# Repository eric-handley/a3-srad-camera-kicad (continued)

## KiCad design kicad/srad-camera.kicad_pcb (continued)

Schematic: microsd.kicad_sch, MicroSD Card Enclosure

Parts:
C151: 100nF; C_0402_1005Metric; LCSC PART NAME C1525
C152: 1uF; C_0603_1608Metric; LCSC PART NAME C15849
C153: 10uF; C_0805_2012Metric; LCSC PART NAME C15850
D3, D4, D5, D6, D7, D8, D9: TVS Vr3.3 Vb4; D_SOD-123F; LCSC PART NAME C19077496
R53, R54, R55, R56, R57, R58: 22R; R_0402_1005Metric; LCSC PART NAME C25092
SD1: MOLEX 472192001; microSD_HC_Molex_47219-2001

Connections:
/MicroSD Port/CLK: R56.1; also elsewhere on the board
/MicroSD Port/CMD: R55.1; also elsewhere on the board
/MicroSD Port/D0: R57.1; also elsewhere on the board
/MicroSD Port/D1: R58.1; also elsewhere on the board
/MicroSD Port/D2: R53.1; also elsewhere on the board
/MicroSD Port/D3: R54.1; also elsewhere on the board
GND: C151.2, C152.2, C153.1, D3.1 (A1), D4.1 (A1), D5.1 (A1), D6.1 (A1), D7.1 (A1), D8.1 (A1), D9.1 (A1), SD1.6 (VSS), SD1.10 (SHIELD); also elsewhere on the board
unnamed: D3.2 (A2), R58.2, SD1.8 (DAT1)
unnamed: D4.2 (A2), R57.2, SD1.7 (DAT0)
unnamed: D5.2 (A2), R56.2, SD1.5 (CLK)
unnamed: D6.2 (A2), R55.2, SD1.3 (CMD)
unnamed: D7.2 (A2), R54.2, SD1.2 (DAT3/CD)
unnamed: D8.2 (A2), R53.2, SD1.1 (DAT2)
VCC_3V3_SD: C151.1, C152.1, C153.2, D9.2 (A2), SD1.4 (VDD); also elsewhere on the board

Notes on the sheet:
DET not needed as MicroSD always present

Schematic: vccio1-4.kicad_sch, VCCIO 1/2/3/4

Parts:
C119: 100nF; C_0402_1005Metric; LCSC PART NAME C1525
U5: RK3566; BGA-565_L15.5-W14.4-P0.40_RK3566_1; MANUFACTURER PART RK3566; JLCPCB PART CLASS Extended Part

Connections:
/MicroSD Port/CLK: U5.G38 (GPIO2_A2_d); also elsewhere on the board
/MicroSD Port/CMD: U5.1E19 (GPIO2_A1_u); also elsewhere on the board
/MicroSD Port/D0: U5.1E20 (GPIO1_D5_u); also elsewhere on the board
/MicroSD Port/D1: U5.1F19 (GPIO1_D6_u); also elsewhere on the board
/MicroSD Port/D2: U5.1D20 (GPIO1_D7_u); also elsewhere on the board
/MicroSD Port/D3: U5.1F18 (GPIO2_A0_u); also elsewhere on the board
/RK3566 SoC/VCCIO_3V3_SD: C119.2, U5.1F17 (VCCIO3); also elsewhere on the board
GND: C119.1; also elsewhere on the board

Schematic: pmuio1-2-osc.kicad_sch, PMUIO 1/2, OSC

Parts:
C98, C101, C104, C106, C108, C110, C111, C112: 100nF; C_0402_1005Metric; LCSC PART NAME C1525
C99, C103, C105, C107, C109: 1uF; C_0603_1608Metric; LCSC PART NAME C15849
C100, C102: 22pF; C_0402_1005Metric; LCSC PART NAME C1555
HSE2: 24MHz; Crystal_SMD_2016-4Pin_2.0x1.6mm; LCSC PART NAME C725986
R37: 22R; R_0402_1005Metric; LCSC PART NAME C25092
R39: 1M; R_0402_1005Metric; LCSC PART NAME C26083
R41: 100R; R_0402_1005Metric; LCSC PART NAME C25076
U5: RK3566; BGA-565_L15.5-W14.4-P0.40_RK3566_1; MANUFACTURER PART RK3566; JLCPCB PART CLASS Extended Part

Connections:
/PMIC_CLK: U5.1T20 (GPIO0_B0_u); also elsewhere on the board
/PMIC_RESETB: C111.2, U5.1R20 (GPIO0_A1_z), U5.AG38 (nPOR_u); also elsewhere on the board
/PMIC_SLEEP: U5.1P19 (GPIO0_A2_d); also elsewhere on the board
/RK3566 SoC/PMUIO 1-2, OSC/XIN: C102.1, HSE2.1, R39.2, U5.AD37 (XIN24M)
/RK3566 SoC/PMUIO 1-2, OSC/XOUT: R37.1, R39.1, U5.AD38 (XOUT24M)
/RK3566 SoC/VCCA_1V8: C107.1, C108.1, U5.1H4 (SYSPLL_AVDD_1V8); also elsewhere on the board
/RK3566 SoC/VCCA_1V8_PMU: C103.2, C104.2, U5.1N18 (PMUPLL_AVDD_1V8); also elsewhere on the board
/RK3566 SoC/VCC_3V3_PMU: C101.2, C112.2, U5.1N15 (PMUIO2), U5.1P16 (PMUIO1); also elsewhere on the board
/RK3566 SoC/VDDA_0V9: C109.1, C110.1, U5.1H5 (SYSPLL_AVDD_0V9); also elsewhere on the board
/RK3566 SoC/VDDA_0V9_PMU: C98.2, C99.2, C105.2, C106.2, U5.1N16 (PMU_VDD_LOGIC_0V9), U5.1P17 (PMUPLL_AVDD_0V9); also elsewhere on the board
/STM_RX/RK_TX: U5.1R18 (GPIO0_C1_d); also elsewhere on the board
/STM_TX/RK_RX: U5.1T19 (GPIO0_C0_d); also elsewhere on the board
GND: C98.1, C99.1, C100.2, C101.1, C102.2, C103.1, C104.1, C105.1, C106.1, C107.2, C108.2, C109.2, C110.2, C111.1, C112.1, HSE2.2, HSE2.4, R41.2, U5.1J5 (SYSPLL_AVSS), U5.1M18 (TVSS), U5.1N17 (PMUPLL_AVSS); also elsewhere on the board
unnamed: C100.1, HSE2.3, R37.2
unnamed: R41.1, U5.AF37 (GPIO0_A4_u)

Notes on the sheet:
SDMMC0_DET
UART0_TX
UART0_RX

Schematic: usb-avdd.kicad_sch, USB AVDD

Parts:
C113, C114, C115, C116, C117, C118: 100nF; C_0402_1005Metric; LCSC PART NAME C1525
R42, R43: 1R; R_0402_1005Metric; LCSC PART NAME C25086
R44: 0R; R_0402_1005Metric; LCSC PART NAME C17168
U5: RK3566; BGA-565_L15.5-W14.4-P0.40_RK3566_1; MANUFACTURER PART RK3566; JLCPCB PART CLASS Extended Part

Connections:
/RK3566 SoC/VCCA_1V8: C113.2, R43.1, U5.1K17 (MULTI_PHY_AVDD_1V8); also elsewhere on the board
/RK3566 SoC/VCC_3V3: R44.1; also elsewhere on the board
/RK3566 SoC/VDDA_0V9: C114.2, R42.1, U5.1K16 (MULTI_PHY_AVDD_0V9); also elsewhere on the board
/USB_DN: U5.R38 (USB_OTG0_DM); also elsewhere on the board
/USB_DP: U5.R37 (USB_OTG0_DP); also elsewhere on the board
/VBUSDET: C115.1, U5.T38 (USB_OTG0_VBUSDET); also elsewhere on the board
GND: C113.1, C114.1, C115.2, C116.1, C117.1, C118.1; also elsewhere on the board
unnamed: C116.2, R42.2, U5.1J17 (USB_AVDD1_0V9)
unnamed: C117.2, R43.2, U5.1H16 (USB_AVDD1_1V8)
unnamed: C118.2, R44.2, U5.1H18 (USB_AVDD1_3V3)

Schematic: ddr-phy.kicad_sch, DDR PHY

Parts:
C88, C89, C90, C93, C94, C95: 100nF; C_0402_1005Metric; LCSC PART NAME C1525
C91, C92, C96, C97: 4.7uF; C_0402_1005Metric; LCSC PART NAME C1779
R36: 120R; R_0402_1005Metric; LCSC PART NAME C25079
U5: RK3566; BGA-565_L15.5-W14.4-P0.40_RK3566_1; MANUFACTURER PART RK3566; JLCPCB PART CLASS Extended Part

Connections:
/MT41K256 DDR3L/A0: U5.1C1 (AC15); also elsewhere on the board
/MT41K256 DDR3L/A1: U5.1B7 (AC18); also elsewhere on the board
/MT41K256 DDR3L/A2: U5.1D2 (AC1); also elsewhere on the board
/MT41K256 DDR3L/A3: U5.1C3 (AC3); also elsewhere on the board
/MT41K256 DDR3L/A4: U5.C1 (AC2); also elsewhere on the board
/MT41K256 DDR3L/A5: U5.B7 (AC9); also elsewhere on the board
/MT41K256 DDR3L/A6: U5.E2 (AC8); also elsewhere on the board
/MT41K256 DDR3L/A7: U5.C2 (AC11); also elsewhere on the board
/MT41K256 DDR3L/A8: U5.A10 (AC7); also elsewhere on the board
/MT41K256 DDR3L/A9: U5.A7 (AC0); also elsewhere on the board
/MT41K256 DDR3L/A10: U5.1A3 (AC10); also elsewhere on the board
/MT41K256 DDR3L/A11: U5.B8 (AC5); also elsewhere on the board
/MT41K256 DDR3L/A12: U5.1A6 (AC19); also elsewhere on the board
/MT41K256 DDR3L/A13: U5.B9 (AC6); also elsewhere on the board
/MT41K256 DDR3L/A14: U5.A9 (AC13); also elsewhere on the board
/MT41K256 DDR3L/BA0: U5.1C2 (AC21); also elsewhere on the board
/MT41K256 DDR3L/BA1: U5.1B6 (AC4); also elsewhere on the board
/MT41K256 DDR3L/BA2: U5.1B3 (AC12); also elsewhere on the board
/MT41K256 DDR3L/CASn: U5.1A2 (AC17); also elsewhere on the board
/MT41K256 DDR3L/CKE: U5.B4 (AC22); also elsewhere on the board
/MT41K256 DDR3L/CK_N: U5.B5 (AC24); also elsewhere on the board
/MT41K256 DDR3L/CK_P: U5.A5 (AC23); also elsewhere on the board
/MT41K256 DDR3L/CSn0: U5.1B5 (AC28); also elsewhere on the board
/MT41K256 DDR3L/DM_A0: U5.1E2 (DDR_DM0_A); also elsewhere on the board
/MT41K256 DDR3L/DM_A1: U5.1G1 (DDR_DM1_A); also elsewhere on the board
/MT41K256 DDR3L/DQ0: U5.G2 (DDR_DQ0_A); also elsewhere on the board
/MT41K256 DDR3L/DQ1: U5.F2 (DDR_DQ1_A); also elsewhere on the board
/MT41K256 DDR3L/DQ2: U5.F1 (DDR_DQ2_A); also elsewhere on the board
/MT41K256 DDR3L/DQ3: U5.E1 (DDR_DQ3_A); also elsewhere on the board
/MT41K256 DDR3L/DQ4: U5.M2 (DDR_DQ4_A); also elsewhere on the board
/MT41K256 DDR3L/DQ5: U5.K1 (DDR_DQ5_A); also elsewhere on the board
/MT41K256 DDR3L/DQ6: U5.K2 (DDR_DQ6_A); also elsewhere on the board
/MT41K256 DDR3L/DQ7: U5.1E1 (DDR_DQ7_A); also elsewhere on the board
/MT41K256 DDR3L/DQ8: U5.P2 (DDR_DQ8_A); also elsewhere on the board
/MT41K256 DDR3L/DQ9: U5.R1 (DDR_DQ9_A); also elsewhere on the board
/MT41K256 DDR3L/DQ10: U5.R2 (DDR_DQ10_A); also elsewhere on the board
/MT41K256 DDR3L/DQ11: U5.T2 (DDR_DQ11_A); also elsewhere on the board
/MT41K256 DDR3L/DQ12: U5.M1 (DDR_DQ12_A); also elsewhere on the board
/MT41K256 DDR3L/DQ13: U5.1F2 (DDR_DQ13_A); also elsewhere on the board
/MT41K256 DDR3L/DQ14: U5.1F1 (DDR_DQ14_A); also elsewhere on the board
/MT41K256 DDR3L/DQ15: U5.1G2 (DDR_DQ15_A); also elsewhere on the board
/MT41K256 DDR3L/DQS_N0: U5.H1 (DDR_DQS0N_A); also elsewhere on the board
/MT41K256 DDR3L/DQS_N1: U5.N2 (DDR_DQS1N_A); also elsewhere on the board
/MT41K256 DDR3L/DQS_P0: U5.H2 (DDR_DQS0P_A); also elsewhere on the board
/MT41K256 DDR3L/DQS_P1: U5.N1 (DDR_DQS1P_A); also elsewhere on the board
/MT41K256 DDR3L/ODT0: U5.1A5 (AC27); also elsewhere on the board
/MT41K256 DDR3L/RASn: U5.1A1 (AC16); also elsewhere on the board
/MT41K256 DDR3L/RESETn: U5.1C7 (AC29); also elsewhere on the board
/MT41K256 DDR3L/VREF_DDR: U5.1H3 (DDR_VREFOUT); also elsewhere on the board
/MT41K256 DDR3L/WEn: U5.1A4 (AC20); also elsewhere on the board
GND: C88.1, C89.1, C90.1, C91.1, C92.1, C93.1, C94.1, C95.1, C96.1, C97.1, R36.1, U5.1D4 (DDR_AVSS); also elsewhere on the board
unnamed: R36.2, U5.1F3 (DDR_RZQ)
VCC_DDR: C88.2, C89.2, C90.2, C91.2, C92.2, C93.2, C94.2, C95.2, C96.2, C97.2, U5.1D5 (DDR_VDDQ_1), U5.1D6 (DDR_VDDQ_2), U5.1D7 (DDR_VDDQ_3), U5.1D8 (DDR_VDDQ_4), U5.1D9 (DDR_VDDQ_5), U5.1E4 (DDR_VDDQ_6), U5.1E6 (DDR_VDDQL_1), U5.1E7 (DDR_VDDQL_2), U5.1E9 (DDR_VDDQL_3), U5.1F4 (DDR_VDDQ_7), U5.1F5 (DDR_VDDQL_4), U5.1G4 (DDR_VDDQ_8), U5.1G5 (DDR_VDDQL_5); also elsewhere on the board

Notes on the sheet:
Caps under package

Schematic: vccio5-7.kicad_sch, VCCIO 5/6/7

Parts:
C85, C86: 100nF; C_0402_1005Metric; LCSC PART NAME C1525
C87: 1nF; C_0402_1005Metric; LCSC PART NAME C1523
R35: 10k; R_0402_1005Metric; LCSC PART NAME C25744
U5: RK3566; BGA-565_L15.5-W14.4-P0.40_RK3566_1; MANUFACTURER PART RK3566; JLCPCB PART CLASS Extended Part

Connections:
/RK3566 SoC/CAM_GPIO0: U5.1T2 (GPIO3_C6_d); also elsewhere on the board
/RK3566 SoC/CAM_GPIO1: U5.AB2 (GPIO4_C0_d); also elsewhere on the board
/RK3566 SoC/CAM_SCL: U5.AD1 (GPIO4_B5_d); also elsewhere on the board
/RK3566 SoC/CAM_SDA: U5.AF1 (GPIO4_B4_d); also elsewhere on the board
/RK3566 SoC/VCCA_1V8: C86.2, R35.2, U5.1D15 (OTP_VCC1V8), U5.1D16 (SARADC_AVDD_1V8); also elsewhere on the board
/RK3566 SoC/VCC_3V3: C85.2, U5.1L4 (VCCIO6_1), U5.1L5 (VCCIO6_2); also elsewhere on the board
GND: C85.1, C86.1, C87.1; also elsewhere on the board
unnamed: C87.2, R35.1, U5.1D17 (SARADC_VIN0)

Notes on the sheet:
I2C2
CIF_CLKOUT

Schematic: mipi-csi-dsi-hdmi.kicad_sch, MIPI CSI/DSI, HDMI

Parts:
C120: 1uF; C_0603_1608Metric; LCSC PART NAME C15849
C121, C122: 100nF; C_0402_1005Metric; LCSC PART NAME C1525
R46: 1R; R_0402_1005Metric; LCSC PART NAME C25086
U5: RK3566; BGA-565_L15.5-W14.4-P0.40_RK3566_1; MANUFACTURER PART RK3566; JLCPCB PART CLASS Extended Part

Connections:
/RK3566 SoC/MIPI_CN: U5.1U9 (MIPI_CSI_RX_CLK0N); also elsewhere on the board
/RK3566 SoC/MIPI_CP: U5.1V9 (MIPI_CSI_RX_CLK0P); also elsewhere on the board
/RK3566 SoC/MIPI_D0_N: U5.AR18 (MIPI_CSI_RX_D0N); also elsewhere on the board
/RK3566 SoC/MIPI_D0_P: U5.AP18 (MIPI_CSI_RX_D0P); also elsewhere on the board
/RK3566 SoC/MIPI_D1_N: U5.AP17 (MIPI_CSI_RX_D1N); also elsewhere on the board
/RK3566 SoC/MIPI_D1_P: U5.AR17 (MIPI_CSI_RX_D1P); also elsewhere on the board
/RK3566 SoC/MIPI_D2_N: U5.AR15 (MIPI_CSI_RX_D2N); also elsewhere on the board
/RK3566 SoC/MIPI_D2_P: U5.AP15 (MIPI_CSI_RX_D2P); also elsewhere on the board
/RK3566 SoC/MIPI_D3_N: U5.AP14 (MIPI_CSI_RX_D3N); also elsewhere on the board
/RK3566 SoC/MIPI_D3_P: U5.AR14 (MIPI_CSI_RX_D3P); also elsewhere on the board
/RK3566 SoC/VCCA_1V8_IMG: C120.2, R46.2; also elsewhere on the board
/RK3566 SoC/VDDA_0V9_IMG: C121.2, U5.1N9 (MIPI_CSI_RX_AVDD_0V9); also elsewhere on the board
GND: C120.1, C121.1, C122.1; also elsewhere on the board
MIPI_AVDD_1V8: C122.2, R46.1, U5.1P9 (MIPI_CSI_RX_AVDD_1V8)

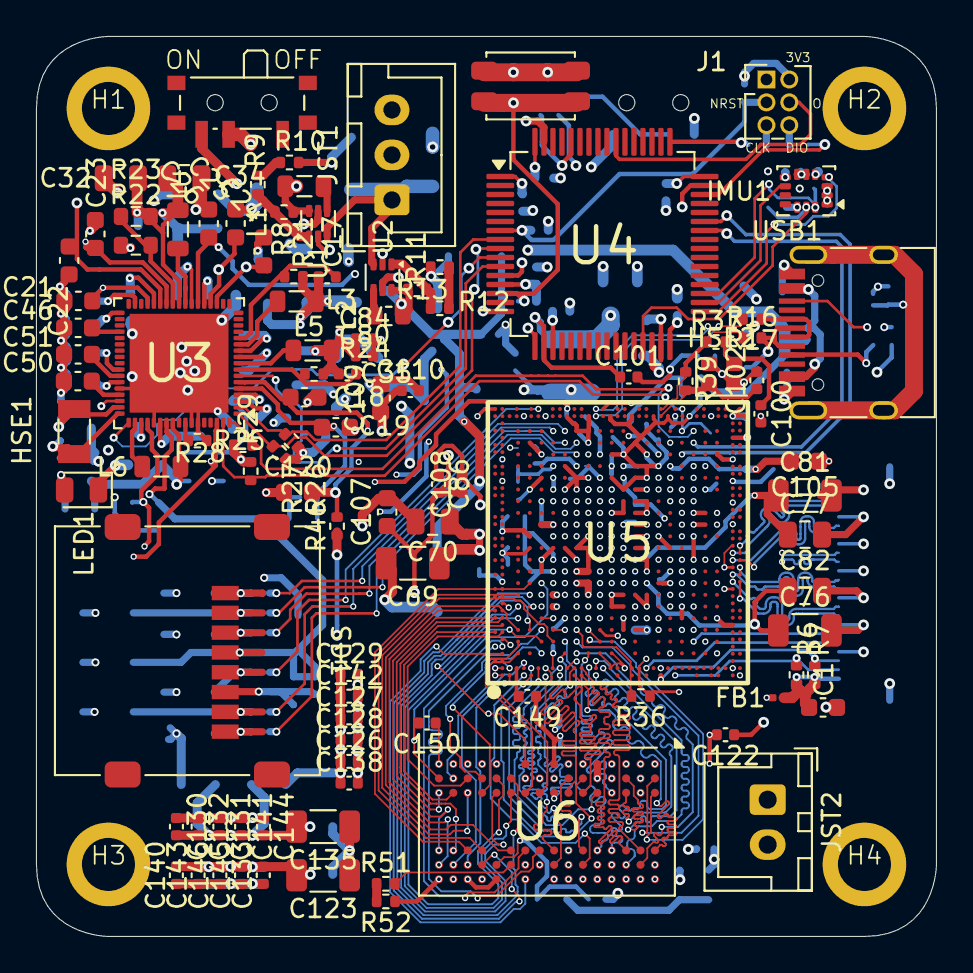
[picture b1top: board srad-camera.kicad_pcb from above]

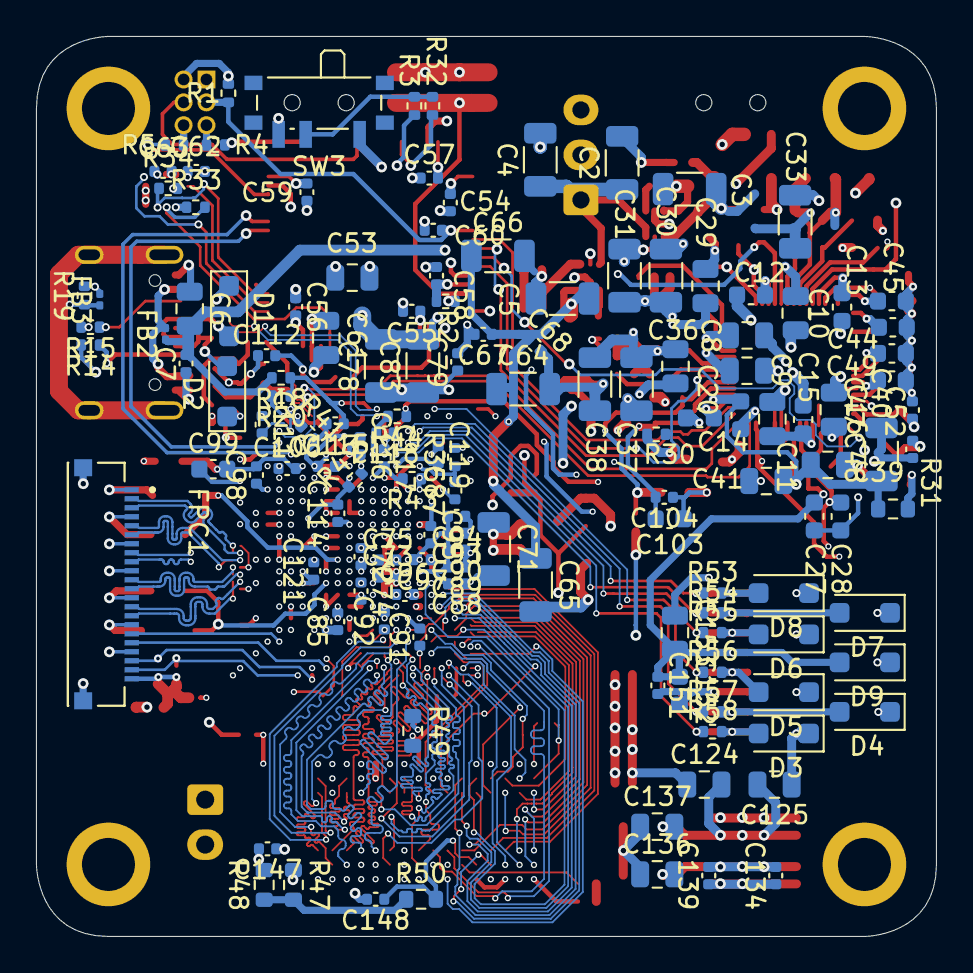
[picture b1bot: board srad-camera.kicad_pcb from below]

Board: 4 copper layers, 50.0 x 50.0 mm, 247 parts (139 on the bottom side), 170 nets.

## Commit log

2025-10-09 STM32 datasheet
2025-10-09 Create block diagram
2025-10-09 New block diagrams
2025-10-09 Initial kicad schematic
2025-10-09 Add schematics
2025-10-09 Add datasheets
2025-10-09 Fix schematic
2025-10-16 Initial RK3566 design
2025-10-16 Create html versions of datasheets, organize in folders
2025-10-25 Wired IMU and USBC, add schematics for RK3566
2025-10-30 Rm old files
2025-10-30 Split schematic to subsheets; wire PMIC, IMU & USB OTG
2025-10-30 Update gitignore
2025-10-30 Switch to 22pin FPC conn
2025-10-30 Clean up root wiring
2025-10-30 Clean up IMU wiring
2025-10-30 Resize sheets
2025-10-30 Draft routing/layout for RK
2025-10-30 Wire peripherals to STM
2025-10-30 Wire microsd port
2025-10-30 Add ports for FC and RK3566
2025-10-30 Minor changes
2025-10-31 Clean up root sheet, add power supply subsheet
2025-10-31 Camera datasheet
2025-10-31 Adjust root sheet
2025-10-31 Update buck converters
2025-10-31 Add power supply and ll shifter
2025-10-31 Make sure logic levels are correct between ICs
2025-10-31 Datasheet for input buck converter
2025-10-31 Add camera product brief
2025-10-31 Remove uneeded level shifter
2025-10-31 Remove SPI between STM and SoC
2025-11-04 Clean up debug connector, STM pinout
2025-11-04 Reconfigure STM32 pinout to work better with physical pin locations
2025-11-04 Added boot + power switch to STM32, user button
2025-11-04 Annotations
2025-11-14 Finalized PMIC and added control from STM32
2025-11-22 Wire up DDR3L
2025-11-22 Annotations + minor tweaks
2025-11-23 Finished wiring RK3566, DDR3L
2025-11-23 Change all sheets to A4, name sheets, split RK3566 into hierarchy
2025-11-23 Mark as R1.0
2025-11-24 Indicate proper feedback trace from SoC
2025-11-24 Swap for standard library symbol
2025-11-24 Minor tweaks + annotations
2025-11-25 Start on PCB design
2025-11-26 Minor tweaks
2025-11-26 Finished wiring PMIC, STM, power input, IMU, FPC
2025-12-02 Remove power/decoupling for unused power domains
2025-12-02 WIP PCB layout
2026-01-13 All major components placed on board
2026-01-14 Allllmost everything placed
2026-01-15 PCB done besides fixing screwups + length matching
2026-01-15 Minor layout tweaks
2026-01-15 More minor layout tweaks
2026-01-15 Length matching for DDL3 LDQS
2026-01-16 Length matching for DDL3 UDQS
2026-01-16 Fix length matching for MIPI
2026-01-17 Update step file
2026-01-18 Restructure repo
2026-01-18 Add reference designs
